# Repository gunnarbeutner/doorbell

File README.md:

# Doorbell controller (STR WF26-compatible)

A drop-in smart replacement for a **WF26 handset** on an **STR Elektronik TV20/S**
apartment-intercom bus, built on an ESP32-S3 running ESPHome. To the building it looks like the
handset it replaces; to Home Assistant it looks like a doorbell, an intercom and a door opener.

## What it does

- **Ring detection** — the front-door bell (Türruf) and the floor button (Etagenruf) are separate
  HA binary sensors and events: phone notifications, presence-aware automations, "someone rang
  while you were out" history.
- **Gong suppression** — a solid-state switch in the chime path mutes the mechanical gong under
  firmware policy (occupancy, quiet hours, do-not-disturb) without touching ring detection, the
  latch/session, codec audio or the door opener. The current interim policy holds that switch open
  for all of suppression mode so a later neighbour gong on shared line 2 cannot reach LS1; this also
  disables physical LS1 listen/talk until the PTT-capable V4.2 hardware and firmware policy are
  fabricated and validated. The switch is normally-closed: if the smart layer dies, the doorbell
  returns to the stock passive path.
- **Door opener from HA** — with the safety in hardware, not firmware: the door relay pair
  replicates the WF26's break-before-make sequence with an RC delay, and an independent hardware
  watchdog releases the door bridge after ~6.7 s no matter what the firmware does. A crashed ESP
  or a runaway automation cannot hold the door open.
- **Two-way audio** — an ES8311 codec taps the bus speech pair through a protected divider (RX)
  and drives the talk line through the same 2.2 kΩ handshake the central expects from a real
  handset (TX). Push-to-talk from HA; wired for HA's Assist voice pipeline.
- **Fully passive fallback** — the original WF26 relay/switch/speaker core is carried on the
  board, hardwired. Gong, listen, talk and door-open all work with the electronics unpowered;
  the smart layer only ever adds, never gates.
- **Local everything** — ESPHome native HA API, OTA updates, on-device web UI. No cloud.

## How the TV20/S bus works

Five wires run from the central to each flat:

| Line | Role |
|------|------|
| 1 | Common — the reference for everything below |
| 2 | Standing **+12 V supply**, current-limited (~90 Ω source), always on |
| 3 | Speech — talk audio toward the door station |
| 4 | **Türruf** — front-door ring |
| 5 | **Etagenruf** — floor-button ring |

A **ring** is the central putting ~12 V on a ring line for about a second; the gong is literally
the handset's speaker driven from that pulse through a capacitor (the floor line rings the
speaker directly). The line-4 pulse also pulls in a relay inside the handset, which **seals
itself in from line 2** and holds line 4 high — that standing level *is* the "call in progress"
state, and the supply rail sags visibly under its load. **Talk** is a 2.2 kΩ bridge from the
speech line to the supply: the central detects exactly that resistance as "off-hook" and routes
audio, which simply rides on top of the DC. The **door opener** is a plain line 2↔3 contact
closure, sequenced break-before-make so the latch drops first. The central ends every session by
sinking line 2 low after a timeout, which drops all latches. A stock handset contains no
electronics at all — a relay, capacitors, switches and a speaker.

The board senses the ring lines with optocouplers, switches its functions with PhotoMOS relays
in the same places the WF26's mechanical switches sat, and leaves the bus model untouched — the
central cannot tell the difference. The full reverse-engineering lives in `DESIGN.md`, the WF26
handset schematic in `wf26/`, and real-bus scope captures in `captures/` — all usable on their
own if you have this intercom family and only want ring detection or muting.

## Beyond the assembled board

The JLCPCB-assembled PCB needs four things it doesn't ship with:

- **Antenna** — the ESP32-S3-WROOM-**1U** has no PCB antenna; any 2.4 GHz u.FL/IPEX antenna
  works (a flex-PCB patch routes nicely out of the enclosure).
- **Speaker/mic transducer (LS1)** — a 16 Ω transducer soldered to the LS1 wire pads. It is the
  gong, the passive listen earpiece and the passive talk mic in one; deliberately not
  board-assembled.
- **JST SH-4 male pigtail for J1** (the deployed power/service inlet) — a pre-crimped SH-4 lead is strongly
  recommended; hand-crimping 1 mm SH contacts is misery.
- **USB power/service lead** — a four-signal USB-A male screw-terminal breakout wired to the J1
  pigtail. Keep D+/D− short and twisted, and verify every conductor before first power-up:
  `docs/design/usb-jst-j1-wiring.svg`.

**Status:** the V4.1 board (JLCPCB-fabbed and -assembled) is bench-verified and deployed —
installed in the wall in place of the WF26, running `firmware/doorbell.yaml`. The smart layer
is powered by a USB wall-wart through its J3 connector; the TV20/S bus powers only the passive
handset core, so the electronics draw nothing from the shared intercom supply. The installed V4.1
USB-C connector mechanically prevents the housing's Talk actuator from fully engaging SW4; the
current V4.2 candidate removes that connector and adds a dry GPIO47 physical-Talk input plus a
mechanical K1 inhibit on SW4's spare pole. Those changed circuits are not field-proven and must pass
the full actuator/cable fit and first-board electrical/timing gates.

## Repository layout

The **KiCad files** (`kicad/doorbell.kicad_sch` / `.kicad_pcb`) are the authoritative source for
the board — edited directly in KiCad. `./build.sh` verifies them and exports the
fab outputs; it does not author or regenerate the board.

| Path | What |
|------|------|
| `REQUIREMENTS.md` | *What* the board must do — functional + safety requirements (start here for intent). |
| `DESIGN.md` | *How* it's built — architecture, GPIO map, relays/SSRs, audio path, bus model. |
| `VERIFICATION.md` | Design-verification gates plus the bench bring-up / commissioning record. |
| `ORDERING.md` | JLCPCB ordering notes (Standard PCBA workflow + the review gates). |
| `kicad/` | Authoritative KiCad project (`doorbell.kicad_sch` / `.kicad_pcb`). See `kicad/README.md`. |
| `tools/` | Build/inspection Python scripts (placement check, routing verify, STEP/BOM/CPL export). |
| `firmware/` | ESPHome configs — `doorbell.yaml` (deployed), `doorbell-bench.yaml` (bench twin: debug SSR switches, audio loopback instrumentation, no HA events), `doorbell-tonegen.yaml` (spare board as bench tone source / HA media player). |
| `sim/` | Node circuit simulator + PCB viewer used to sanity-check the design (`cd sim`; `npm test`). |
| `wf26/` | Reverse-engineered WF26 handset (`wf26.kicad_sch`). |
| `captures/` | Bench scope captures of the real TV20/S (ring, door-open, timeout) + web viewer. |
| `docs/` | Datasheets and reference docs (`datasheets/`, `design/`, `ordering/`) — incl. the wall wire-up map (`design/wall-wiring-v4.svg`) and the J1 power/service-cable pinout (`design/usb-jst-j1-wiring.svg`). |
| `fab/` | Generated fab outputs (Gerbers, drill, BOM, CPL, STEP) — produced by `./build.sh`. |
| `orders/` | Shipped fabrication order archives. |

## Build

```bash
./build.sh             # verify (ERC/DRC/placement/routing/simulation) + export fab outputs
./build.sh verify      # run the same checks without updating generated artifacts
```

See `kicad/README.md` for the build pipeline details.

## Firmware

```bash
cd firmware
esphome run doorbell.yaml    # needs firmware/secrets.yaml (see below)
```

Secrets (WiFi credentials, API encryption key, OTA password) live in `firmware/secrets.yaml`,
which is gitignored — create it with `wifi_ssid`, `wifi_password`, `api_encryption_key` and
`ota_password` before building. Run `esphome clean` after switching configs or renaming a device
— a stale build directory fails the build in confusing ways.

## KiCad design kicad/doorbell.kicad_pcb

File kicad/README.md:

# Doorbell controller — KiCad project

## Build pipeline (verify + fab; the KiCad files are authoritative)

`doorbell.kicad_sch` / `doorbell.kicad_pcb` are the authoritative source — edit them in
KiCad. `build.sh` never authors copper; it runs the checks KiCad's own DRC/ERC can't
express and exports the fab outputs:

```
./build.sh              # verify + all order-ready exports (full release)
./build.sh verify       # ERC + placement + PCB/DRC + simulation; no exports
./build.sh schematic    # schematic ERC + PDF export
./build.sh pcb          # placement + planes/thieving/connectivity + DRC
./build.sh simulation   # circuit-simulator tests
./build.sh fabrication  # Gerbers + drill + position + BOM -> fab/
./build.sh step         # populated STEP model
./build.sh board-step   # bare-board STEP model
```

| Script | Interpreter | Role |
|--------|-------------|------|
| `tools/check_pcb.py` | KiCad bundled python (pcbnew) | verify placement (edge flush/overhang, parts inside outline) |
| `tools/route.py` | KiCad bundled python (pcbnew) | refill zones + verify connectivity + copper-thieving sliver limit |
| `tools/jlcpcb_cpl.py` | KiCad bundled python (pcbnew) | JLCPCB CPL (pad-centroid positions) |
| `tools/jlcpcb_files.py` | `.venv/bin/python` (kiutils) | JLCPCB BOM (from the schematic) |

`tools/doorbell_design.py` holds the placement constants `check_pcb.py` verifies — connector edge
fit/overhang and the mounting-hole MLCC keep-out; the KiCad files are authoritative for the rest.
The board is hand-routed **in KiCad**;
`route.py` fails the build on any unrouted connection or any copper-thieving float island
over the sliver limit (≥ 2 mm² or ≥ 10 mm) — fix those in KiCad, never with a tool.

> 4-layer, ~64 × 59 mm; `tools/check_pcb.py` gates placement (the edge connectors J1/J2/J3 and U1
> sit flush on their board edges).

## Where the rest lives (deliberately not duplicated here)

This README is only the build/verify/fab process. Everything else stays in its authoritative
source so it can't drift out of sync — so there is **no part list, net list, or pin table here**:

- **Parts / values / footprints / LCSC numbers** — in the schematic (hidden `LCSC`/`MPN`/`Footprint`
  fields); exported to `fab/doorbell-bom-jlcpcb.csv` by `build.sh fabrication`.
- **Net connectivity and pin assignments** — `doorbell.kicad_sch` (open it, or
  `kicad-cli sch export netlist`).
- **Architecture, pin map, relays/SSRs, audio path, power, isolation, layout** — `../DESIGN.md`;
  the requirements it satisfies — `../REQUIREMENTS.md`; ordering — `../ORDERING.md`.

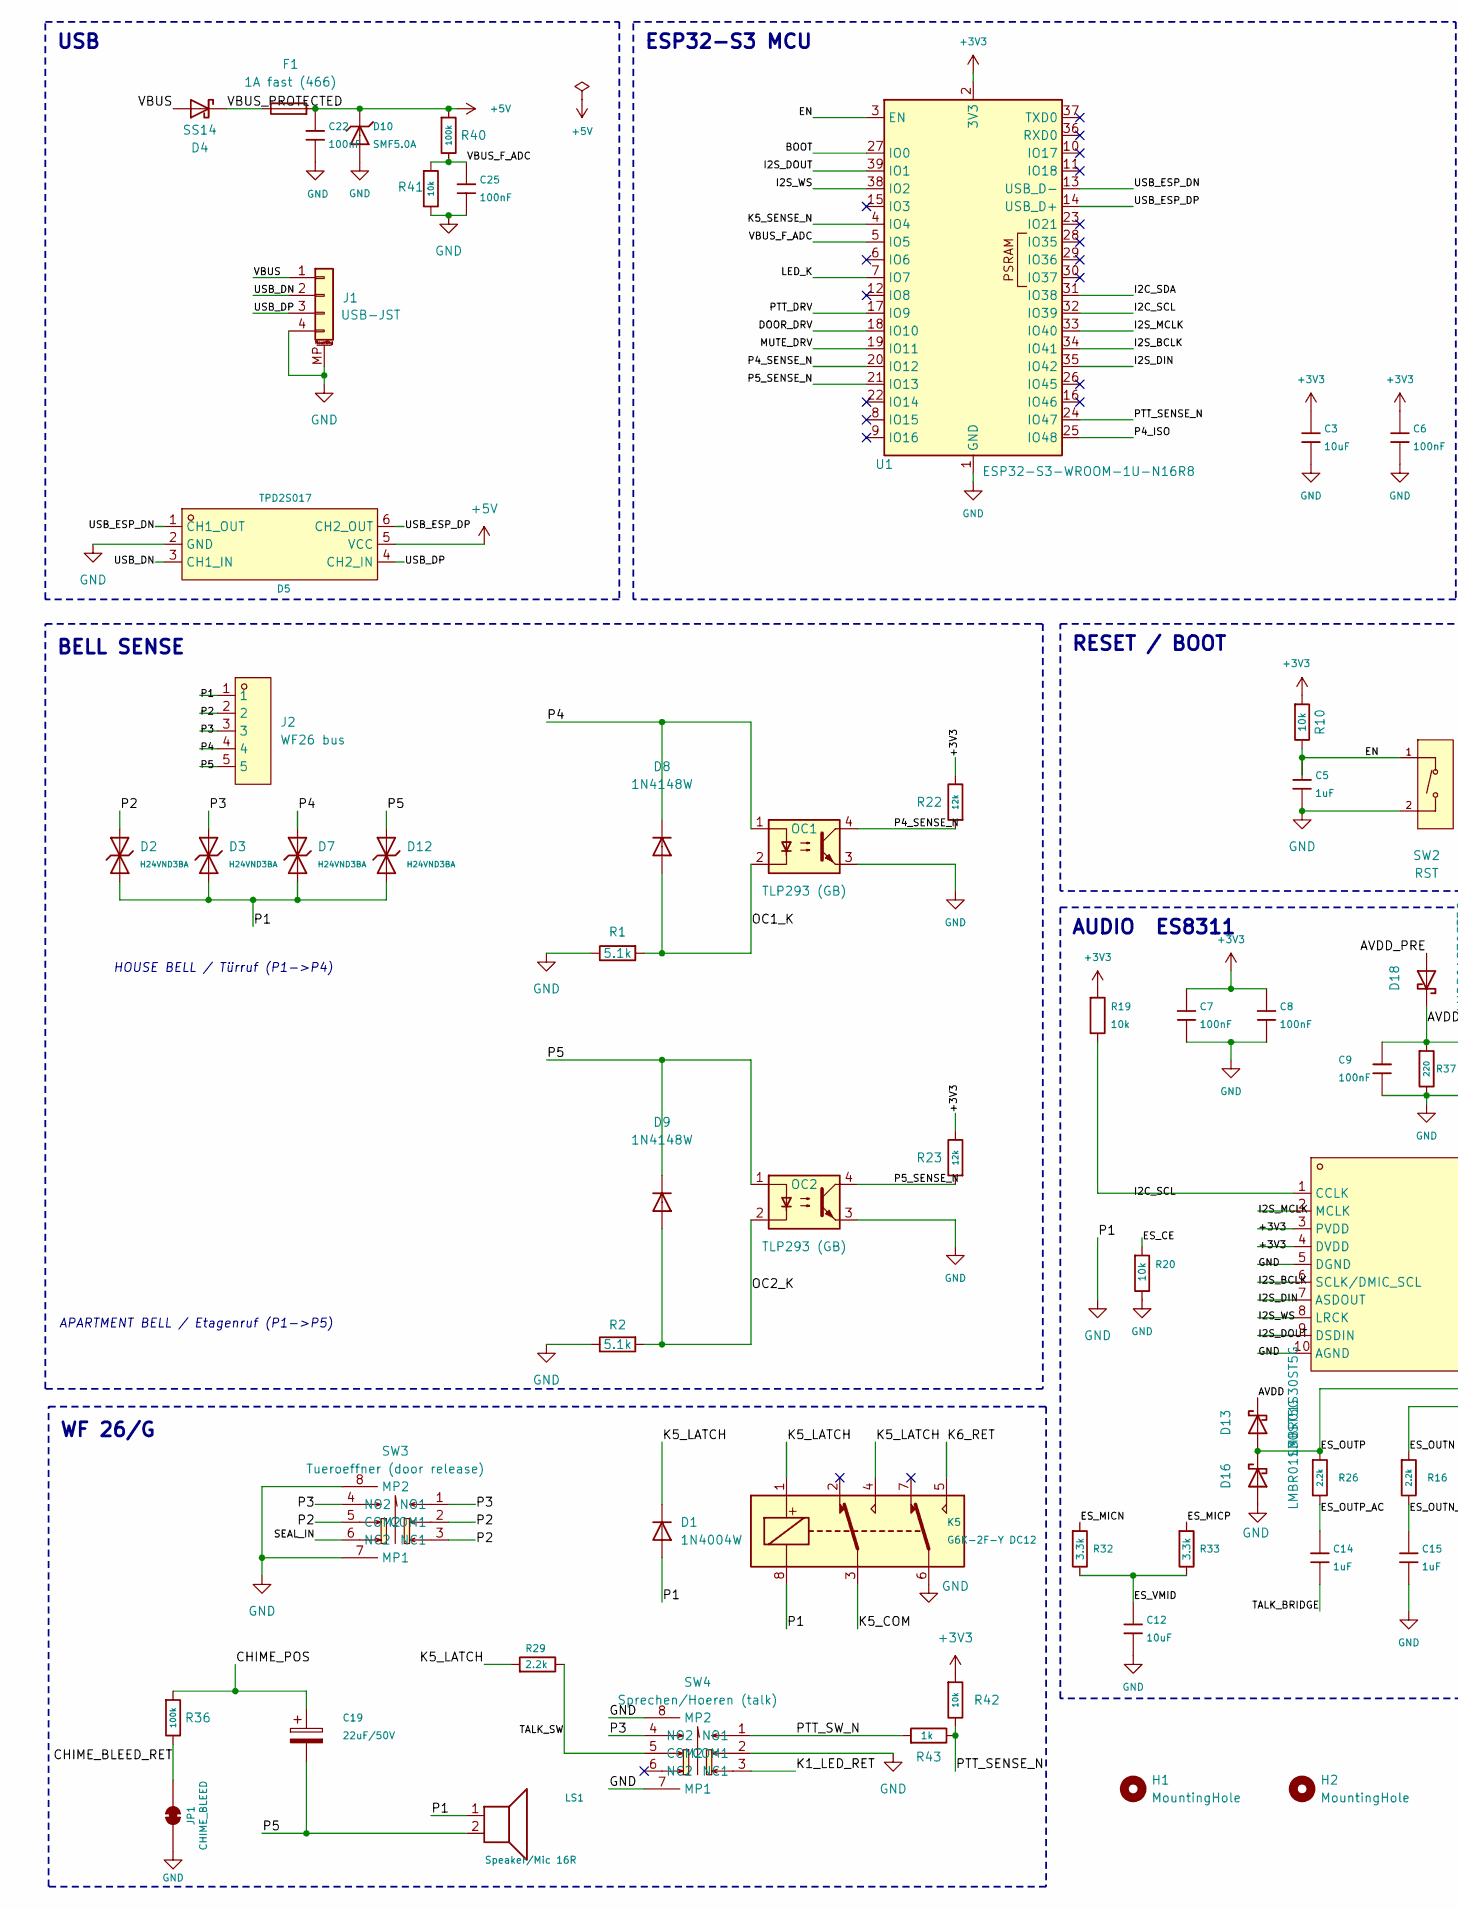
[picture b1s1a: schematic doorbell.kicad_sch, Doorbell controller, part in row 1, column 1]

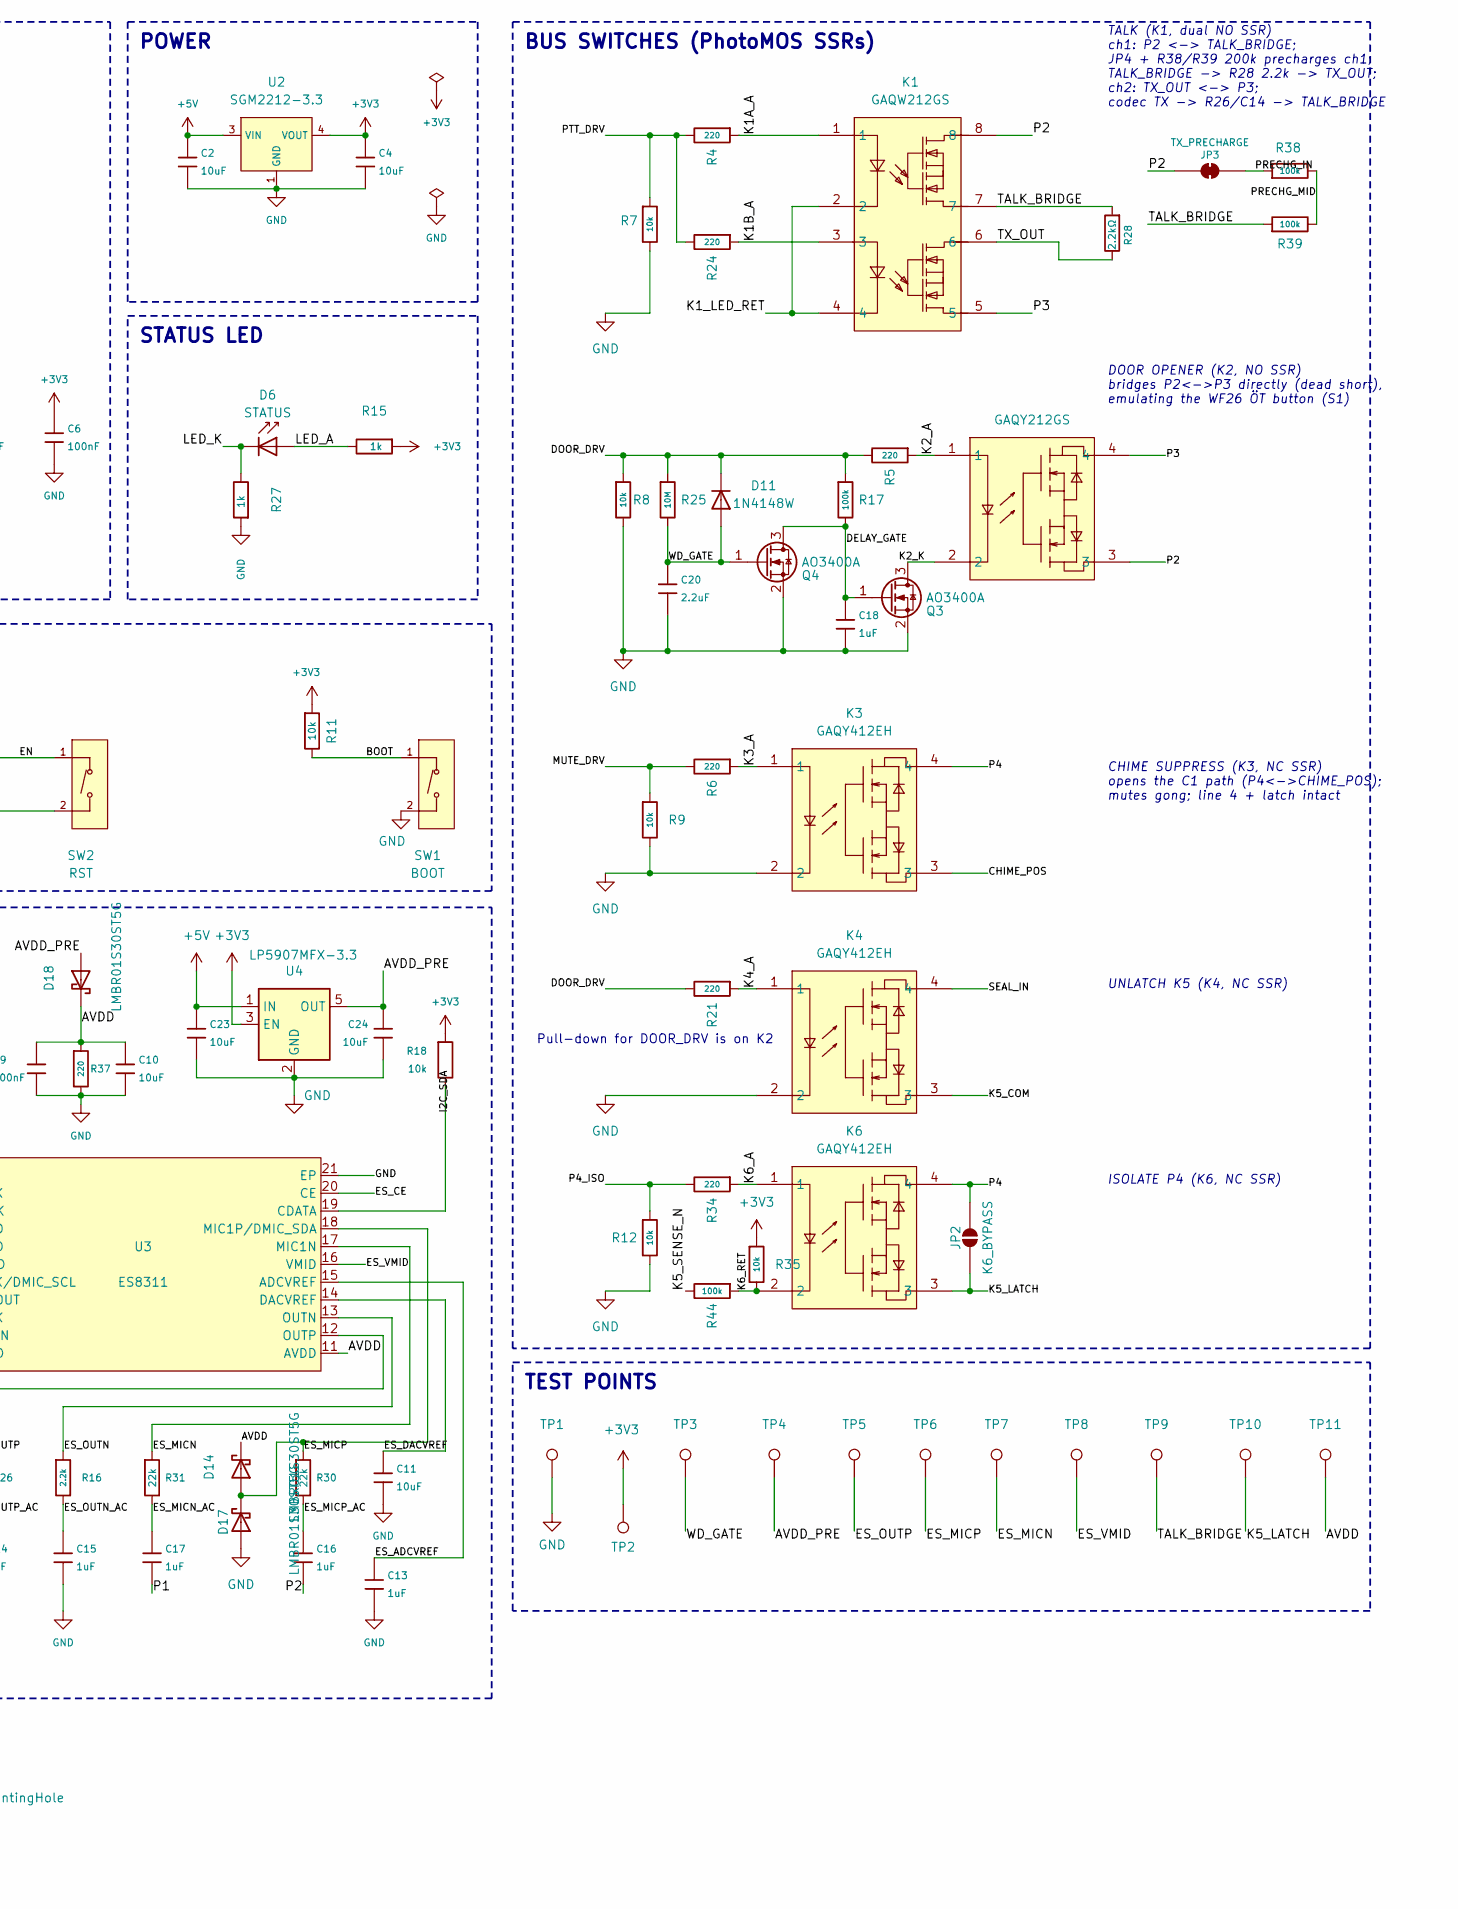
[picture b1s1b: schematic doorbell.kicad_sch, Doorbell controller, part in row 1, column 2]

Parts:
C2, C3, C4, C10, C11, C12, C23, C24: 10uF; C_0603; MPN CL10A106KP8NNNC; LCSC C19702
C5, C13, C14, C15, C16, C17, C18: 1uF; C_0603; MPN CL10A105KB8NNNC; LCSC C15849
C6, C7, C8, C9, C22, C25: 100nF; C_0603; MPN CC0603KRX7R9BB104; LCSC C14663
C19: 22uF/50V; CAP-SMD_BD6.3-L6.6-W6.6-FD; MPN EEEFK1H220P; LCSC C128458
C20: 2.2uF; C_0603; MPN CL10A225KO8NNNC; LCSC C23630
D1: 1N4004W; SOD-123FL_L2.7-W1.8-LS3.8-RD; MPN 1N4004W; LCSC C18199087
D2, D3, D7, D12: H24VND3BA; D_SOD-323; Part H24VND3BA; LCSC C20615815
D4: SS14; D_SMA; MPN SS14; LCSC C2480
D5: TPD2S017; SOT-23-6_L2.9-W1.6-P0.95-LS2.8-BL; MPN TPD2S017DBVR; LCSC C880115
D6: STATUS; D_0603; MPN KT-0603R; LCSC C2286
D8, D9, D11: 1N4148W; D_SOD-123; MPN 1N4148W; LCSC C81598
D10: SMF5.0A; D_SOD-123FL; MPN SMF5.0A; LCSC C19077497
D13, D14, D16, D17, D18: LMBR01S30ST5G; X3-DFN0603-2_L0.6-W0.3-RD; MPN LMBR01S30ST5G; LCSC C383224
F1: 1A fast (466); Fuse_1206_3216Metric; LCSC C151135
H1, H2: MountingHole; MountingHole_3.2mm_M3
J1: USB-JST; JST_SH_SM04B-SRSS-TB_1x04-1MP_P1.00mm_Horizontal; MPN SM04B-SRSS-TB(LF)(SN); LCSC C160404
J2: WF26 bus; CONN-TH_5P-P3.50_DORABO_DB125-3.5-5P-GN-S; MPN DB125-3.5-5P-GN-S; LCSC C3646874
JP1: CHIME_BLEED; SolderJumper-2_P1.3mm_Bridged_RoundedPad1.0x1.5mm
JP2: K6_BYPASS; SolderJumper-2_P1.3mm_Open_RoundedPad1.0x1.5mm
JP3: TX_PRECHARGE; SolderJumper-2_P1.3mm_Bridged_RoundedPad1.0x1.5mm
K1: GAQW212GS; SOP-8_L9.8-W4.4-P2.54-LS6.8-BL; MPN GAQW212GS; LCSC C7435123
K2: GAQY212GS; SOP-4_L4.3-W4.4-P2.54-LS6.8-TR; MPN GAQY212GS; LCSC C7435107
K3, K4, K6: GAQY412EH; SMD-4_L4.8-W6.4-P2.54-LS9.6-BL; MPN GAQY412EH; LCSC C7435135
K5: G6K-2F-Y DC12; Relay_DPDT_Omron_G6K-2F-Y; MPN G6K-2F-Y DC12; LCSC C397194
LS1: Speaker/Mic 16R; SolderWire-0.5sqmm_1x02_P4.6mm_D0.9mm_OD2.1mm
OC1, OC2: TLP293 (GB); SOP-4_L4.4-W2.8-P1.27-LS7.0-BR; MPN TLP293(GB-TPL,E; LCSC C77656
Q3, Q4: AO3400A; SOT-23; MPN AO3400A; LCSC C20917
R1, R2: 5.1k; R_0603; MPN 0603WAF5101T5E; LCSC C23186
R4, R5, R6, R21, R24, R34: 220; R_0603; LCSC C22962
R7, R8, R9: 10k; R_0402; Overload Voltage (Max) 75V; Tolerance ±1%; Part 0603WAF1002T5E; LCSC C25744
R10, R11, R18, R19, R20: 10k; R_0402; MPN 0603WAF1002T5E; LCSC C25744
R12, R35, R41, R42: 10k; R_0402; Overload Voltage (Max) 50V; Tolerance ±1%; Part 0402WGF1002TCE; LCSC C25744
R15, R27, R43: 1k; R_0603; MPN 0603WAF1001T5E; LCSC C21190
R16, R26: 2.2k; R_0603; Overload Voltage (Max) 75V; Tolerance ±1%; Part 0603WAF2201T5E; LCSC C4190
R17, R36, R38, R39, R40, R44: 100k; R_0603; LCSC C25803
R22, R23: 12k; R_0402; MPN 0402WGF1202TCE; LCSC C25752
R25: 10M; R_0603; LCSC C7250
R28: 2.2kΩ; R_0603; MPN 0603WAF2201T5E; LCSC C4190
R29: 2.2k; R_0603; MPN 0603WAF2201T5E; LCSC C4190
R30, R31: 22k; R_0603; MPN 0603WAF2202T5E; LCSC C31850
R32, R33: 3.3k; R_0603; MPN 0603WAF3301T5E; LCSC C22978
R37: 220; R_0603_1608Metric; MPN 0603WAF2200T5E; LCSC C22962
SW1: BOOT; SW_TS-1088-AR02016; MPN TS-1088-AR02016; LCSC C720477
SW2: RST; SW_TS-1088-AR02016; MPN TS-1088-AR02016; LCSC C720477
SW3: Tueroeffner (door release); SW-TH_SPPJ322300; MPN SPPJ322300; LCSC C398940
SW4: Sprechen/Hoeren (talk); SW-TH_SPPJ322300; MPN SPPJ322300; LCSC C398940
TP1: GND; TestPoint_Pad_D1.5mm
TP2: +3V3; TestPoint_Pad_D1.5mm
TP3: WD_GATE; TestPoint_Pad_D1.5mm
TP4: AVDD_PRE; TestPoint_Pad_D1.5mm
TP5: ES_OUTP; TestPoint_Pad_D1.5mm
TP6: ES_MICP; TestPoint_Pad_D1.5mm
TP7: ES_MICN; TestPoint_Pad_D1.5mm
TP8: ES_VMID; TestPoint_Pad_D1.5mm
TP9: TALK_BRIDGE; TestPoint_Pad_D1.5mm
TP10: K5_LATCH; TestPoint_Pad_D1.5mm
TP11: AVDD; TestPoint_Pad_D1.5mm
U1: ESP32-S3-WROOM-1U-N16R8; ESP32-S3-WROOM-1U; MPN ESP32-S3-WROOM-1U-N16R8; LCSC C3013946
U2: SGM2212-3.3; SOT-223-3_L6.5-W3.4-P2.30-LS7.0-BR; LCSC C3294699
U3: ES8311; WQFN-20_L3.0-W3.0-P0.40-BL-EP1.7; MPN ES8311; LCSC C962342
U4: LP5907MFX-3.3; SOT-23-5; MPN LP5907MFX-3.3/NOPB; LCSC C80670

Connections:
+3V3: C3.1, C4.1, C6.1, C7.1, C8.1, R10.1, R11.1, R15.1, R18.1, R19.1, R22.2, R23.2, R35.1, R42.1, TP2.1 (1_1), U1.2 (3V3), U2.2 (VOUT), U2.4 (VOUT), U3.3 (PVDD), U3.4 (DVDD), U4.3 (EN)
+5V: C2.1, C22.1, C23.1, D5.5 (VCC), D10.1, F1.2, R40.1, U2.3 (VIN), U4.1 (IN)
/AVDD: C9.1, C10.1, D13.1, D14.1, D18.1, R37.1, TP11.1 (1_1), U3.11 (AVDD)
/AVDD_PRE: C24.1, D18.2, TP4.1 (1_1), U4.5 (OUT)
/BOOT: R11.2, SW1.1 (A), U1.27 (IO0)
/CHIME_BLEED_RET: JP1.2 (B), R36.2
/CHIME_POS: C19.1, K3.3, R36.1
/DELAY_GATE: C18.1, Q3.1 (G), Q4.3 (D), R17.2
/DOOR_DRV: D11.1, R5.2, R8.1, R17.1, R21.2, R25.1, U1.18 (IO10)
/EN: C5.1, R10.2, SW2.1 (A), U1.3 (EN)
/ES_ADCVREF: C13.1, U3.15 (ADCVREF)
/ES_CE: R20.1, U3.20 (CE)
/ES_DACVREF: C11.1, U3.14 (DACVREF)
/ES_MICN: R31.1, R32.1, TP7.1 (1_1), U3.17 (MIC1N)
/ES_MICN_AC: C17.1, R31.2
/ES_MICP: D14.2, D17.1, R30.1, R33.1, TP6.1 (1_1), U3.18 (MIC1P/DMIC_SDA)
/ES_MICP_AC: C16.1, R30.2
/ES_OUTN: R16.1, U3.13 (OUTN)
/ES_OUTN_AC: C15.1, R16.2
/ES_OUTP: D13.2, D16.1, R26.1, TP5.1 (1_1), U3.12 (OUTP)
/ES_OUTP_AC: C14.1, R26.2
/ES_VMID: C12.1, R32.2, R33.2, TP8.1 (1_1), U3.16 (VMID)
/I2C_SCL: R19.2, U1.32 (IO39), U3.1 (CCLK)
/I2C_SDA: R18.2, U1.31 (IO38), U3.19 (CDATA)
/I2S_BCLK: U1.34 (IO41), U3.6 (SCLK/DMIC_SCL)
/I2S_DIN: U1.35 (IO42), U3.7 (ASDOUT)
/I2S_DOUT: U1.39 (IO1), U3.9 (DSDIN)
/I2S_MCLK: U1.33 (IO40), U3.2 (MCLK)
/I2S_WS: U1.38 (IO2), U3.8 (LRCK)
/K1A_A: K1.1, R4.1
/K1B_A: K1.3, R24.1
/K1_LED_RET: K1.2, K1.4, SW4.3 (NC1)
/K2_A: K2.1, R5.1
/K2_K: K2.2, Q3.3 (D)
/K3_A: K3.1, R6.1
/K4_A: K4.1, R21.1
/K5_COM: K4.3, K5.3
/K5_LATCH: D1.1 (K), JP2.1 (A), K5.1, K5.4, K6.3, R29.1, TP10.1 (1_1)
/K5_SENSE_N: R44.2, U1.4 (IO4)
/K6_A: K6.1, R34.1
/K6_RET: K5.5, K6.2, R35.2, R44.1
/LED_A: D6.2, R15.2
/LED_K: D6.1, R27.2, U1.7 (IO7)
/MUTE_DRV: R6.2, R9.1, U1.19 (IO11)
/OC1_K: D8.2, OC1.2, R1.1
/OC2_K: D9.2, OC2.2, R2.1
/P2: C16.2, D2.2, J2.2, JP3.1 (A), K1.8, K2.3, SW3.2 (COM1), SW3.3 (NC1), SW3.5 (COM2)
/P3: D3.2, J2.3, K1.5, K2.4, SW3.1 (NO1), SW3.4 (NO2), SW4.4 (NO2)
/P4: D7.2, D8.1, J2.4, JP2.2 (B), K3.4, K6.4, OC1.1
/P4_ISO: R12.1, R34.2, U1.25 (IO48)
/P4_SENSE_N: OC1.4, R22.1, U1.20 (IO12)
/P5: C19.2, D9.1, D12.2, J2.5, LS1.2, OC2.1
/P5_SENSE_N: OC2.4, R23.1, U1.21 (IO13)
/PRECHG_IN: JP3.2 (B), R38.1
/PRECHG_MID: R38.2, R39.2
/PTT_DRV: R4.2, R7.1, R24.2, U1.17 (IO9)
/PTT_SENSE_N: R42.2, R43.2, U1.24 (IO47)
/PTT_SW_N: R43.1, SW4.1 (NO1)
/SEAL_IN: K4.4, SW3.6 (NC2)
/TALK_BRIDGE: C14.2, K1.7, R28.2, R39.1, TP9.1 (1_1)
/TALK_SW: R29.2, SW4.5 (COM2)
/TX_OUT: K1.6, R28.1
/USB_DN: D5.3 (CH1_IN), J1.2
/USB_DP: D5.4 (CH2_IN), J1.3
/USB_ESP_DN: D5.1 (CH1_OUT), U1.13 (USB_D-)
/USB_ESP_DP: D5.6 (CH2_OUT), U1.14 (USB_D+)
/VBUS: D4.2, J1.1
/VBUS_F_ADC: C25.1, R40.2, R41.1, U1.5 (IO5)
/VBUS_PROTECTED: D4.1, F1.1
/WD_GATE: C20.1, D11.2, Q4.1 (G), R25.2, TP3.1 (1_1)
GND: C2.2, C3.2, C4.2, C5.2, C6.2, C7.2, C8.2, C9.2, C10.2, C11.2, C12.2, C13.2, C15.2, C17.2, C18.2, C20.2, C22.2, C23.2, C24.2, C25.2, D1.2 (A), D2.1, D3.1, D5.2 (GND), D7.1, D10.2, D12.1, D16.2, D17.2, J1.4, J1.MP (MountPin), J2.1, JP1.1 (A), K3.2, K4.2, K5.6, K5.8, LS1.1, OC1.3, OC2.3, Q3.2 (S), Q4.2 (S), R1.2, R2.2, R7.2, R8.2, R9.2, R12.2, R20.2, R27.1, R37.2, R41.2, SW1.2 (B), SW2.2 (B), SW3.7 (MP1), SW3.8 (MP2), SW4.2 (COM1), SW4.7 (MP1), SW4.8 (MP2), TP1.1 (1_1), U1.1 (GND), U1.40 (GND), U1.41 (GND), U2.1 (GND), U3.5 (DGND), U3.10 (AGND), U3.21 (EP), U4.2 (GND)

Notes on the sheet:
AUDIO ES8311
STATUS LED
Pull-down for DOOR_DRV is on K2
ISOLATE P4 (K6, NC SSR)
USB
UNLATCH K5 (K4, NC SSR)
RESET / BOOT
BUS SWITCHES (PhotoMOS SSRs)
BELL SENSE
WF 26/G
TALK (K1, dual NO SSR) ch1: P2 <-> TALK_BRIDGE; JP4 + R38/R39 200k precharges ch1; TALK_BRIDGE -> R28 2.2k -> TX_OUT; ch2: TX_OUT <-> P3; codec TX -> R26/C14 -> TALK_BRIDGE
CHIME SUPPRESS (K3, NC SSR) opens the C1 path (P4<->CHIME_POS); mutes gong; line 4 + latch intact
TEST POINTS
HOUSE BELL / Türruf (P1->P4)
DOOR OPENER (K2, NO SSR) bridges P2<->P3 directly (dead short), emulating the WF26 ÖT button (S1)
APARTMENT BELL / Etagenruf (P1->P5)
POWER
ESP32-S3 MCU

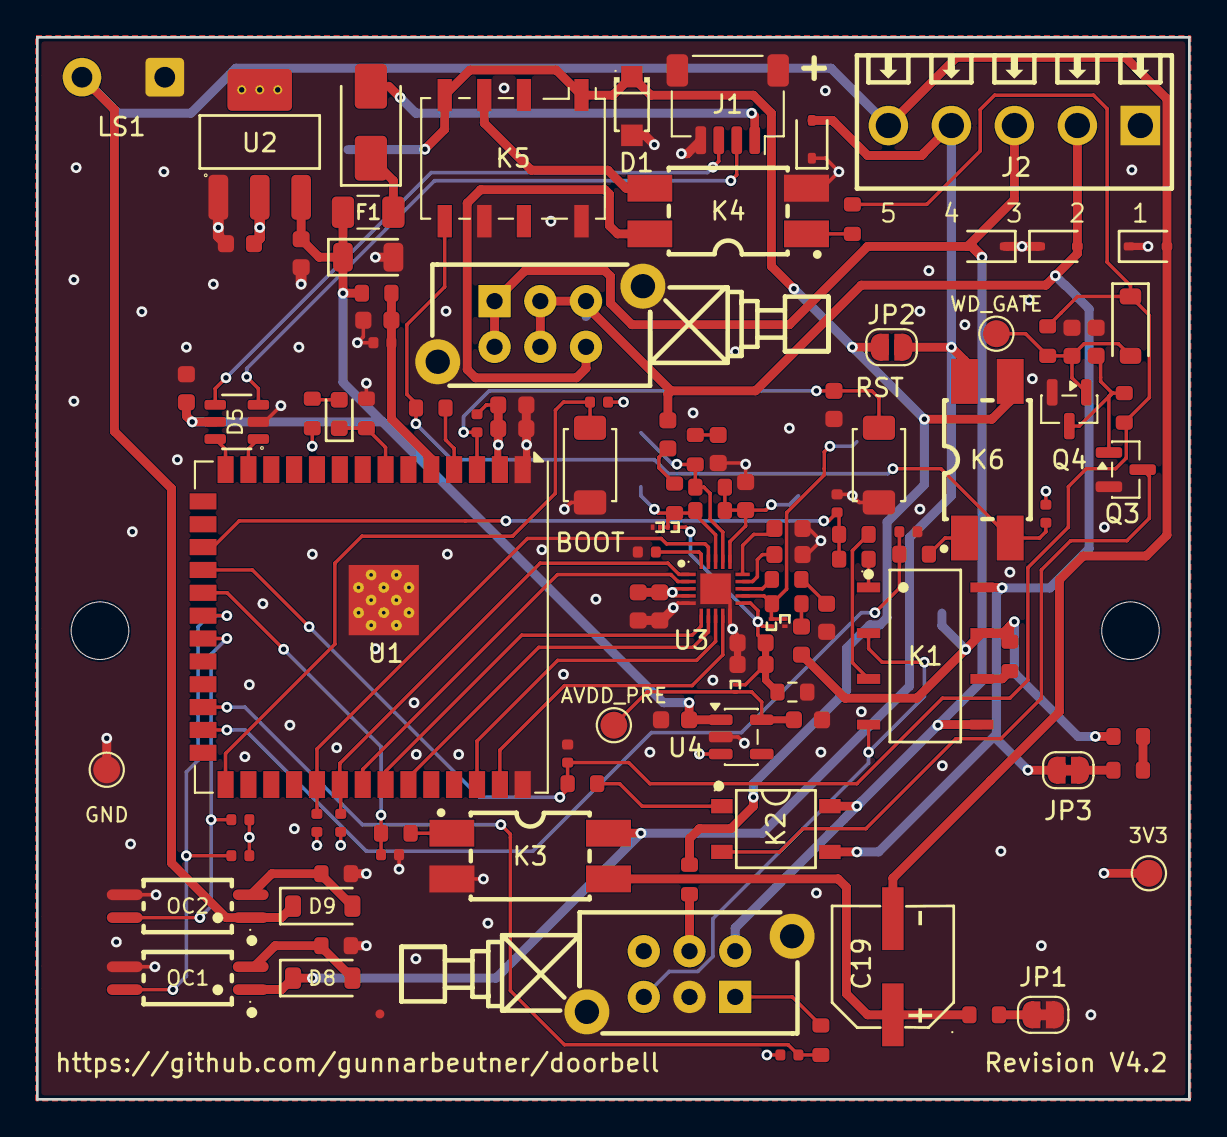
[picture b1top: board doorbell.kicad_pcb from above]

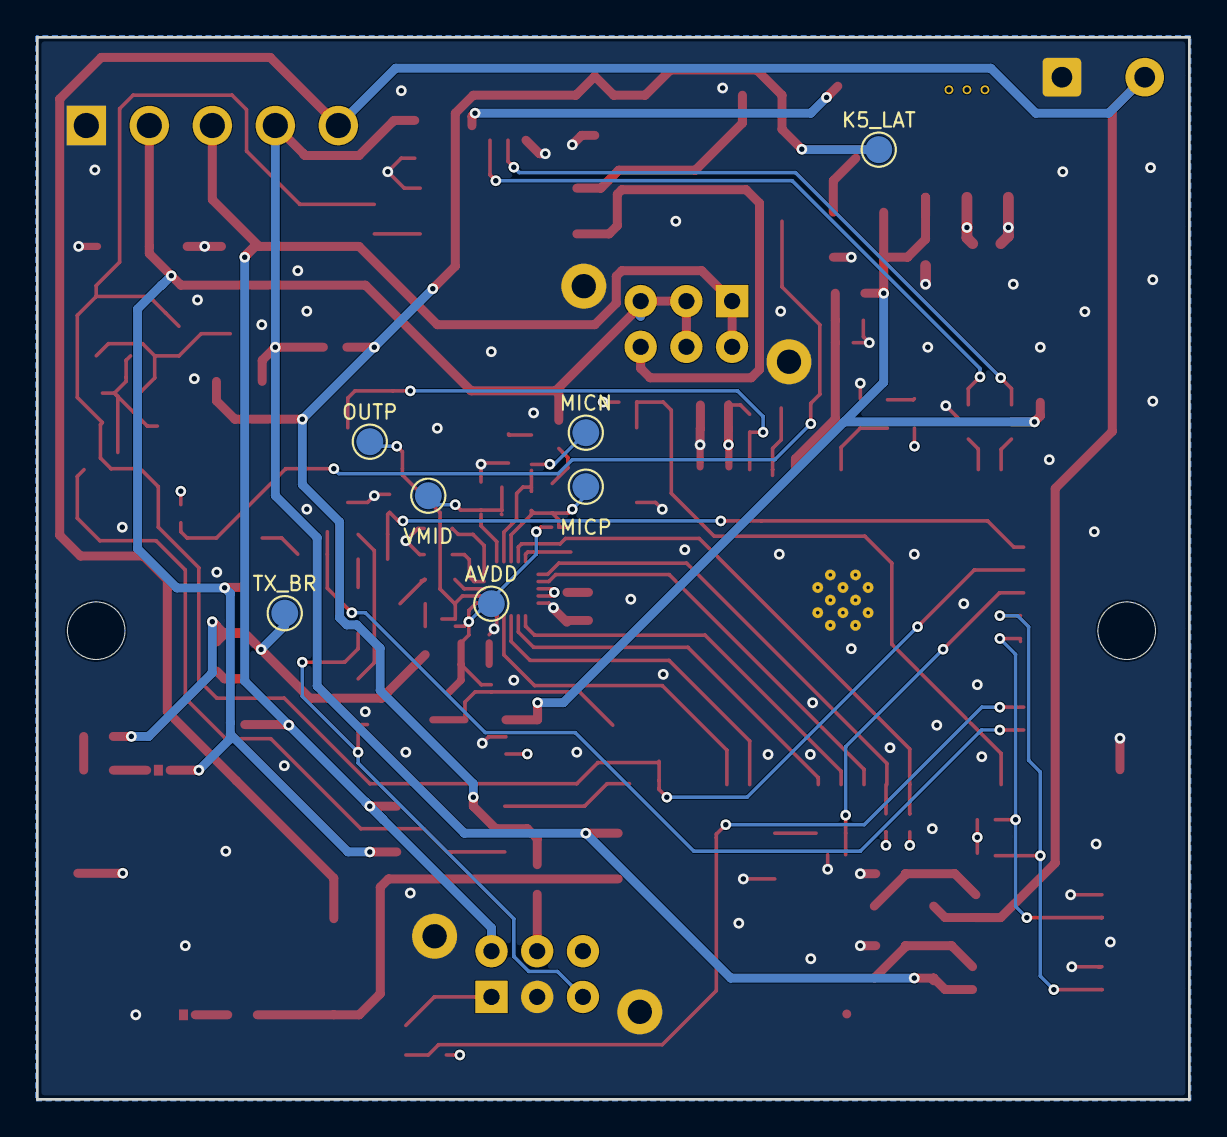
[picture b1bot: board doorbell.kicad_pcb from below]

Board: 4 copper layers, 64.0 x 59.0 mm, 119 parts (7 on the bottom side), 71 nets.

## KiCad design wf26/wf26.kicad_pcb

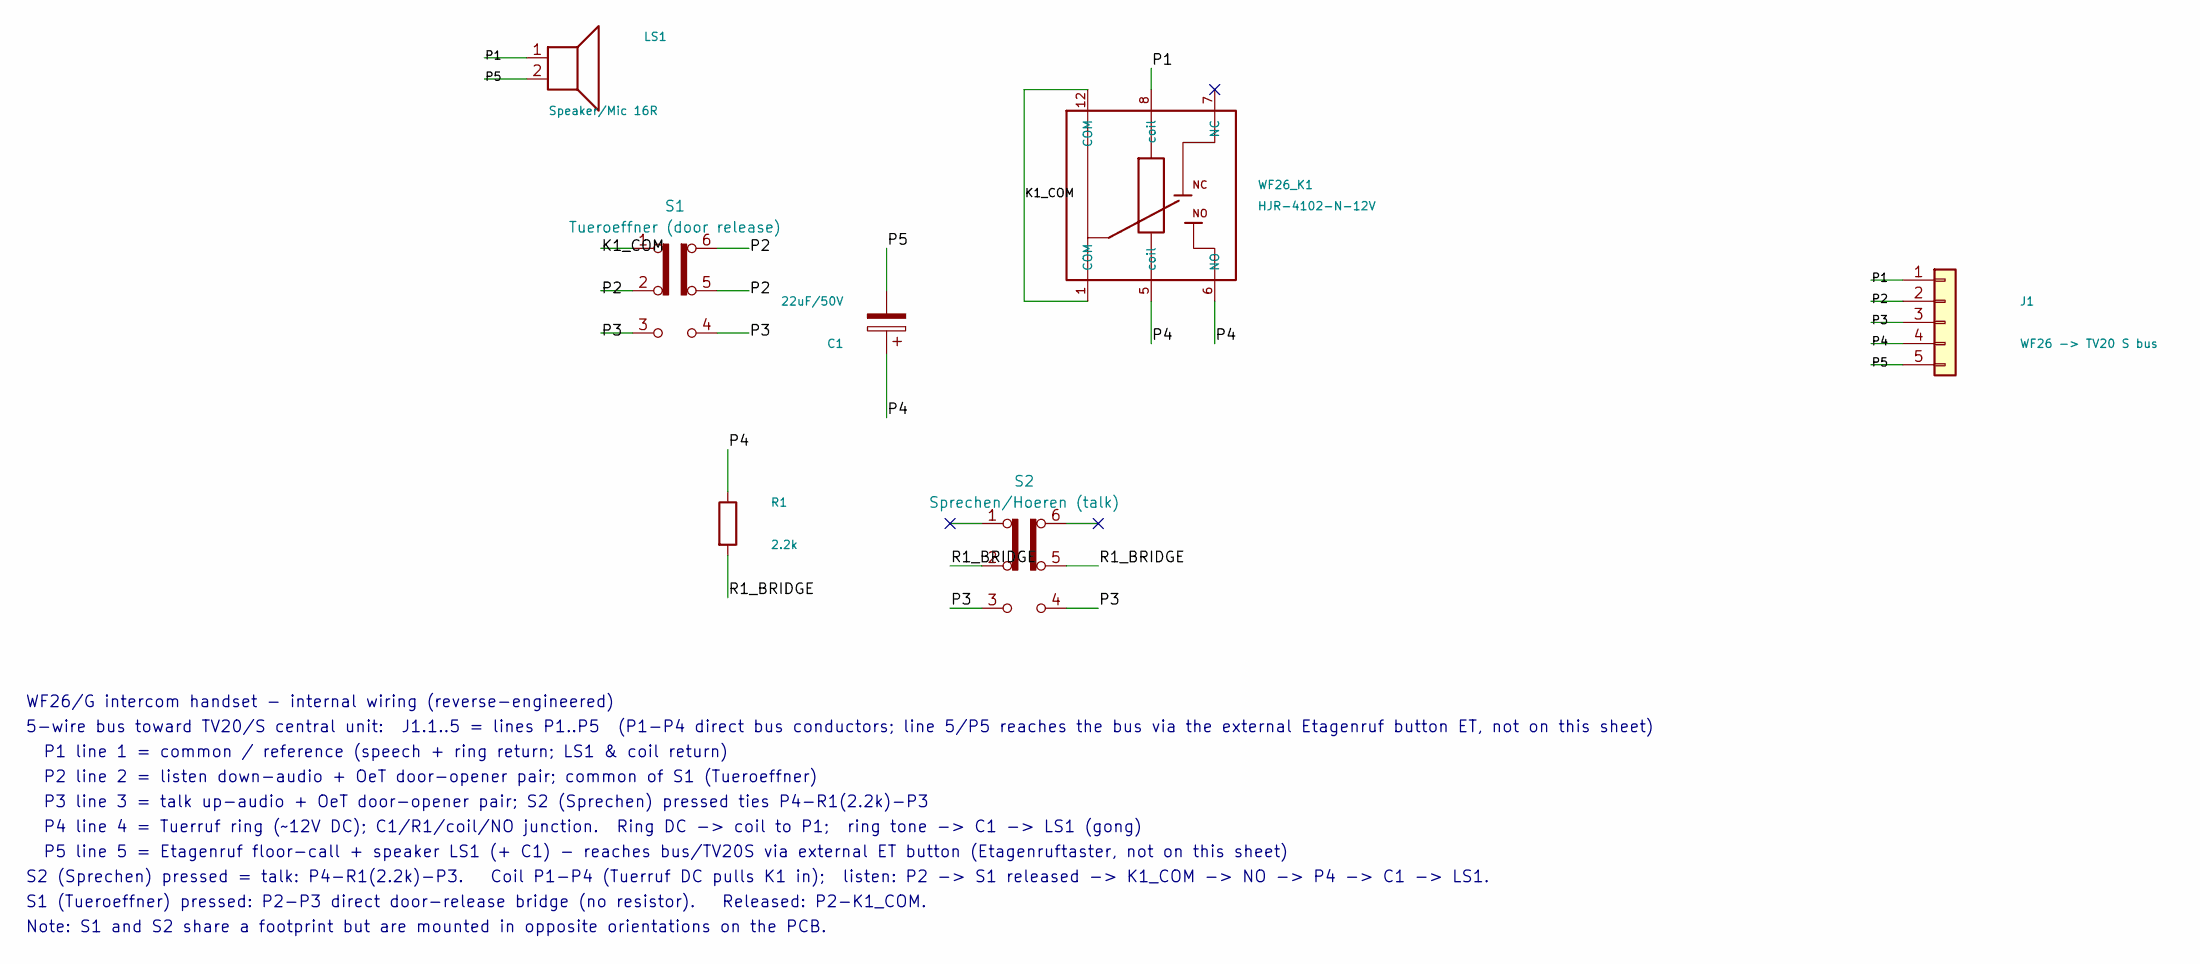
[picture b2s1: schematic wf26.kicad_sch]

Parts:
C1: 22uF/50V; CP_Radial_D5.0mm_P2.00mm
J1: WF26 -> TV20 S bus; TerminalBlock_Phoenix_PT-1,5-5-3.5-H_1x05_P3.50mm_Horizontal
LS1: Speaker/Mic 16R; PinHeader_1x02_P2.54mm_Vertical
R1: 2.2k; R_Axial_DIN0207_L6.3mm_D2.5mm_P7.62mm_Horizontal
S1: Tueroeffner (door release); SW_CK_JS202011CQN_DPDT_Straight
S2: Sprechen/Hoeren (talk); SW_CK_JS202011CQN_DPDT_Straight
WF26_K1: HJR-4102-N-12V; Relay_SPDT_HJR-4102

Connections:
/K1_COM: S1.1 (A), WF26_K1.1 (COM), WF26_K1.12 (COM)
/P1: J1.1, LS1.1, WF26_K1.8 (coil)
/P2: J1.2, S1.2 (B), S1.5 (B), S1.6 (C)
/P3: J1.3, S1.3 (C), S1.4 (A), S2.3 (C), S2.4 (A)
/P4: C1.1, J1.4, R1.1, WF26_K1.5 (coil), WF26_K1.6 (NO)
/P5: C1.2, J1.5, LS1.2
/R1_BRIDGE: R1.2, S2.2 (B), S2.5 (B)

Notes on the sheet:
S2 (Sprechen) pressed = talk: P4-R1(2.2k)-P3. Coil P1-P4 (Tuerruf DC pulls K1 in); listen: P2 -> S1 released -> K1_COM -> NO -> P4 -> C1 -> LS1.
P4 line 4 = Tuerruf ring (~12V DC); C1/R1/coil/NO junction. Ring DC -> coil to P1; ring tone -> C1 -> LS1 (gong)
5-wire bus toward TV20/S central unit: J1.1..5 = lines P1..P5 (P1-P4 direct bus conductors; line 5/P5 reaches the bus via the external Etagenruf button ET, not on this sheet)
P1 line 1 = common / reference (speech + ring return; LS1 & coil return)
P5 line 5 = Etagenruf floor-call + speaker LS1 (+ C1) - reaches bus/TV20S via external ET button (Etagenruftaster, not on this sheet)
Note: S1 and S2 share a footprint but are mounted in opposite orientations on the PCB.
S1 (Tueroeffner) pressed: P2-P3 direct door-release bridge (no resistor). Released: P2-K1_COM.
P2 line 2 = listen down-audio + OeT door-opener pair; common of S1 (Tueroeffner)
P3 line 3 = talk up-audio + OeT door-opener pair; S2 (Sprechen) pressed ties P4-R1(2.2k)-P3
WF26/G intercom handset - internal wiring (reverse-engineered)

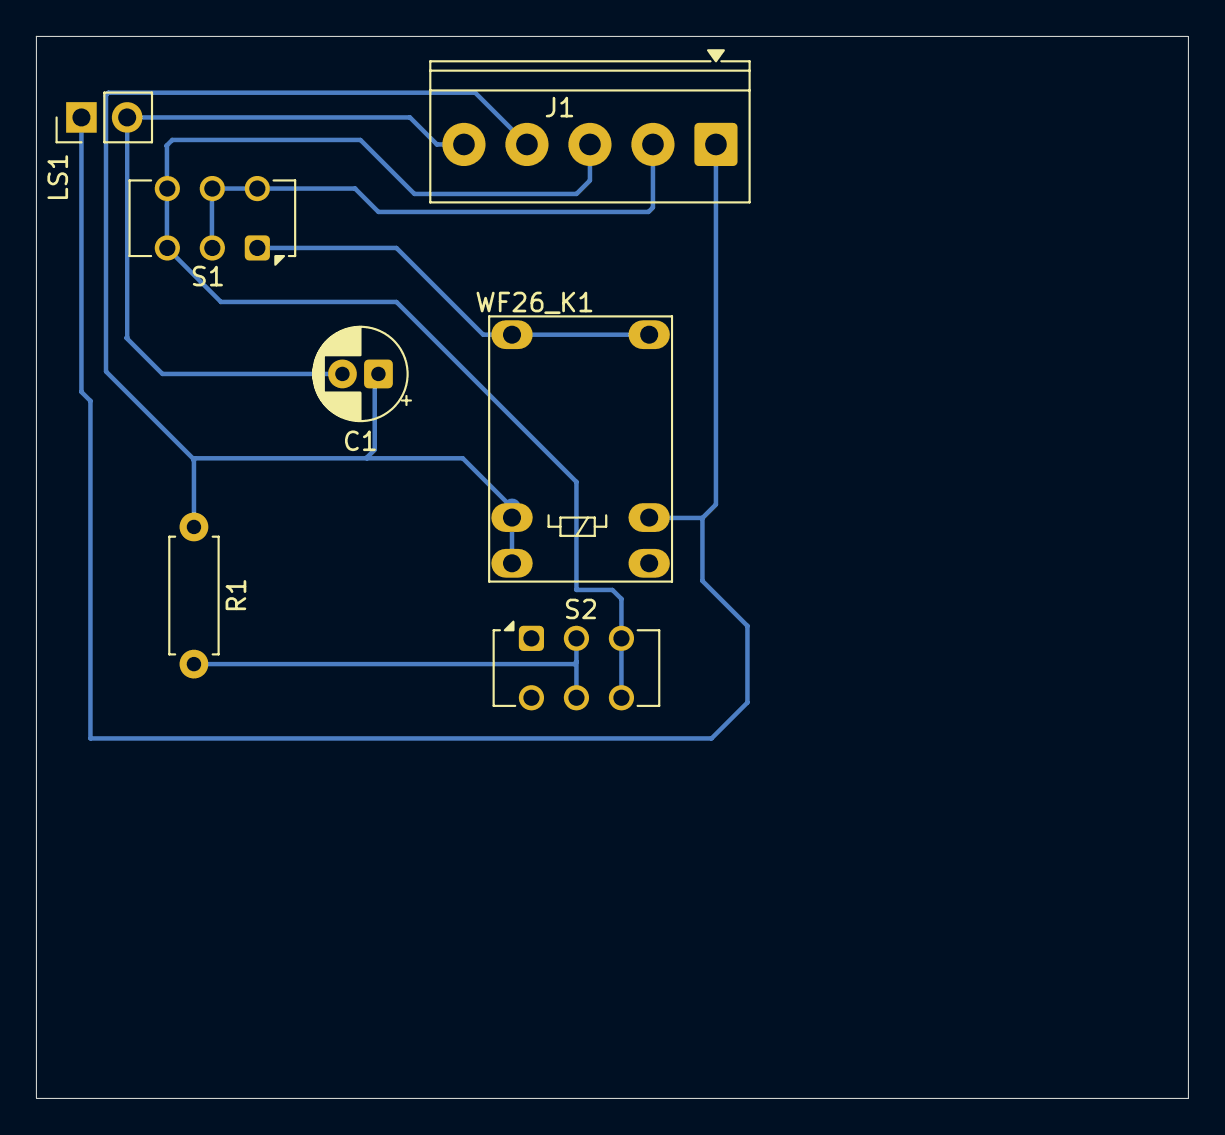
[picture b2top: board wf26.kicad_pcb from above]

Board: 2 copper layers, 64.0 x 59.0 mm, 7 parts (0 on the bottom side), 7 nets.

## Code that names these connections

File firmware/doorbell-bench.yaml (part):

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# GPIO map (S3-WROOM-1U; USB on the north edge, the ES8311 I2C/I2S bus ascending down the codec edge):
#   House Doorbell     (OC1 / Türruf sense)        : GPIO12
#   Apartment Doorbell (OC2 / Etagenruf sense)     : GPIO13
#   front_door_buzzer  (DOOR_DRV → K2+K4 door pair) : GPIO10
#   suppress_chime_bin (K3 / chime suppress)       : GPIO11
#   K1                 (PTT SSR, talk=energised)   : GPIO9
#   K5_SENSE_N        (K5 aux NO via R44, active-low) : GPIO4
#   P4_ISO            (K6 request, active-high)   : GPIO48
#   post-fuse +5 V monitor (VBUS_F_ADC / ADC1_CH4) : GPIO5
#   status LED          (active-low D6)             : GPIO7
#   I2C_SDA  (ES8311 control)                      : GPIO38
#   I2C_SCL  (ES8311 control)                      : GPIO39
#   I2S_MCLK (master clock)                        : GPIO40
#   I2S_BCLK (bit clock, SCLK)                     : GPIO41
#   I2S_DIN  (capture, ASDOUT)                     : GPIO42
#   I2S_WS   (LRCK)                                : GPIO2
#   I2S_DOUT (DAC / playback, DSDIN)               : GPIO1
#   logger                                         : native USB-Serial-JTAG (GPIO19/GPIO20 = USB D-/D+)
# The ES8311 bus is ordered ascending by module pad — SDA,SCL,MCLK,BCLK,DIN on GPIO38-42, then WS,DOUT
# on GPIO2/GPIO1 — so it fans out down U1's codec edge with no crossings, matching U3's pin sequence.
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
i2c:
  id: codec_i2c            # referenced by the on_boot DAC soft-ramp override (REG0x37)
  sda: GPIO38              # I2C_SDA — ES8311 (U3) control bus
  scl: GPIO39              # I2C_SCL — ES8311 (U3) control bus
  scan: false

i2s_audio:
  id: i2s_bus
  i2s_lrclk_pin: GPIO2    # I2S_WS / LRCK
  i2s_bclk_pin: GPIO41    # I2S_BCLK / SCLK
  i2s_mclk_pin: GPIO40    # I2S_MCLK

audio_dac:
  - platform: es8311
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    i2s_audio_id: i2s_bus
    dac_type: external
    audio_dac: es8311_codec
    i2s_dout_pin: GPIO1    # I2S_DOUT / DSDIN (ESP→codec, playback)
    sample_rate: 32000
    keep_alive: true       # local port of esphome/esphome#15565, pinned to ESPHome 2026.7.0

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    restore_mode: ALWAYS_OFF
  # Stage-2d only, after Stage-2a has proved unpowered P4 continuity and passive K5 seal-in. This
  # requests K6 open; K5's auxiliary contact gates the hardware LED return, so P4_ISO alone cannot
  # open the fail-closed P4 path before K5 physically pulls in. GPIO4 senses K6_RET only through
  # R44 = 100 kΩ; even a driven-low sense pin cannot supply normal K6 operating current.
  - platform: output
    name: "Debug P4 Isolation"
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# suppressed) — exactly what the gate pull-downs are there to prevent.
output:
  - platform: gpio
    pin: GPIO9               # K1 — PTT SSR (energised = talk: P2↔TALK_BRIDGE handshake + TX_OUT↔P3 gate, codec→C14→R26→P3)
    id: ptt_relay_bin
  - platform: gpio
    pin: GPIO11              # K3 — chime suppress (open C1: P4↔CHIME_POS)
    id: suppress_chime_bin
  - platform: gpio
    pin: GPIO10              # DOOR_DRV — door pair: K2 bridges P2↔P3 (ÖT), K4 breaks the seal-in to
                             # drop the WF26 latch; K2's make is delayed ~38ms (Q3/RC) so the break
                             # leads on a freshly armed assertion. TODO.md tracks production command
                             # serialization, K1/K6 hand-off and the required 500ms low re-arm time.
    id: front_door_buzzer_bin
  - platform: gpio
    pin: GPIO48              # P4_ISO — K6 opens only when K5's aux contact grounds K6_RET
    id: p4_isolation_req

button:
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
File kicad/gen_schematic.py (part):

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G = 2.54
SCHEM_POS = {
    # --- USB-C: TPD2S017 flow-through ESD clamp below J1 (connects by labels: J1-side
    #     USB_DP/USB_DM in, ESP-side *_ESP out), CC terminators wired off the CC pins ---
    "J1": (19, 20), "D_esd": (18.5, 34.5),  # ESD clamp low enough that its pin labels
                                            # clear J1's GND hookup, high enough that
                                            # its body clears the box bottom
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wire(_p15, (265.43, _p15[1]), (265.43, _ca1[1]), _ca1)
# VMID reservoir + CE pull-down sit in the pocket left of U3's bottom edge and
# connect by label (a wire would have to cross the whole bend field). The pin-16
# label gets NO stub: "ES_VMID" then ends 0.5 mm short of the MIC1N bend vertical;
# pin 20's row is above the bend tops, so its auto label is safe. The pocket parts
# carry hand-placed horizontal labels off their pin-1 tips.
add_label("ES_VMID", *PX("U3", "16"), 0, stub=0)
add_label("ES_VMID", *PX("C_vmid", "1"), 0, stub=1.27)
add_label("ES_CE", *PX("R_ce", "1"), 0, stub=1.27)
SKIP_LABEL_PINS.update({("U3", "16"), ("C_vmid", "1"), ("R_ce", "1")})

# ---- LDO: C_in/C_out wired inline on the VIN/VOUT pin row. U2's own rail pins are
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SKIP_LABEL_PINS.update({("U3", "19"), ("R_sda", "2"), ("U3", "1"), ("R_scl", "2")})
_sda2, _scl2 = PX("R_sda", "2"), PX("R_scl", "2")
wire(PX("U3", "19"), (_sda2[0], PX("U3", "19")[1]), _sda2)
add_label("I2C_SDA", _sda2[0], 168.91, 90, stub=0)
wire(PX("U3", "1"), (_scl2[0], PX("U3", "1")[1]), _scl2)
add_label("I2C_SCL", 168.91, PX("U3", "1")[1], 0, stub=0)

# ---- opto collector pull-ups: each R_pu* stands on its opto's pin-4 stub (pin 1
#      dead on the collector row, pin 2 = +3V3 up). The OC*_OUT net keeps its pin-4
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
